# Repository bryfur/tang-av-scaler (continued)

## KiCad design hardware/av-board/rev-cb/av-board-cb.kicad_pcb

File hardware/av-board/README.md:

# The AV board (rev C-B)

The scaler's hardware, for the sixth generation of game consoles: a Sipeed Tang Mega 138K SOM (Gowin
GW5AST-138, with its DDR3 and configuration flash) on a carrier of its own, 100 x 100 mm, four
layers, about 290 parts. Built (JLCPCB) and running the scaler since 2026-11.

| On the board | Part | For |
|---|---|---|
| Component video in (three RCA jacks) | ADV7181D decoder | the console's YPbPr, sampled line-locked: 16-bit 4:2:2 to the FPGA; also wired: RGB with SCART sync, a VGA header (RGBHV with DDC): not used by the gateware yet |
| Stereo audio in (two RCA jacks) | PCM1808 converter, on its own 4.5 V supply | the console's sound, to HDMI |
| S/PDIF in (a header: coax or an optical module) | a slicer | not used by the gateware yet |
| HDMI out | SN65DP159 between the FPGA's transceivers and the receptacle (run as a redriver), ESD arrays, DDC/HPD/CEC | up to 4K60 by the link's rate; the scaler sends 1080p60 |
| Clock | MS5351M generator | the transceivers' reference, trimmed by the scaler to keep the output in step with the input; the audio converter's clock |
| Control | a Seeed XIAO ESP32-C5 in sockets, through level translators | Wi-Fi and the web page; the FPGA's JTAG (it loads bitstreams) and a UART and SPI port to it |
| Power | USB-C, 5 V / 3 A; a buck and LDOs | 3.3 V, 1.8 V, 1.1 V and the analogue rails |
| Test access | J17 (I2C buses and six spare FPGA pins behind 220 R), J16 (JTAG), rail test pads | [rev-cb/README.md](rev-cb/README.md) |

The design, connection by connection with its sources: [rev-c/design.md](rev-c/design.md) (the
SOM's interface, power, the clock generator, the XIAO, HDMI) and, for the circuits taken from the
earlier rev B (the decoder's front end, the audio converter, the supplies),
[older/rev-b/design.md](older/rev-b/design.md). Reviewed against every part's data sheet:
[rev-c/review.md](rev-c/review.md), [older/rev-b/review.md](older/rev-b/review.md). Fab files and
ordering notes: [rev-cb/README.md](rev-cb/README.md). The FPGA's pins:
`rev-cb/fpga/av-board-cb.cst` (generated from the board).

The board is generated with KiCad's Python API from `rev-cb/board.py`; nothing is drawn by hand.

## Layout of this directory

| Path | What |
|---|---|
| `rev-cb/` | the board: `board.py` (its parts and nets: the one source the schematic and PCB are generated from), `gen_pcb.py` (outline, placement, routing passes), the generated KiCad project, `fab/` (JLCPCB Gerbers, BOM, CPL), `img/` (renders), `fpga/` (pin constraints) |
| `rev-c/` | what rev C-B shares with its sibling C-A: the circuit (`carrier.py`), floor plan and layout, the SOM's interface (`som.py`, `som-pinout.csv`, `check_som_fp.py`), the FPGA pin assignment (`pinmap.py`), `design.md`, `review.md` |
| `kit/` | the generators and checks (below), and the circuits and layout taken from rev B: `circuits.py` (the supplies, the ADV7181D front end, the PCM1808, the S/PDIF input, the XIAO, the HDMI receptacle), `adv7181d_layout.py`, `tmds_layout.py` |
| `lib/` | LCSC symbols and footprints (3D models not in git) |
| `refs/` | data sheets and reference designs (not in git) |
| `older/` | the revisions before this one (A, B: hats on Sipeed's Tang Console; C-A: with an ADV7511): not built, kept for their design notes and reviews. [older/README.md](older/README.md) |

## Making the board

Everything is generated from `rev-cb/board.py`; edit that (and `gen_pcb.py` for placement), not
the KiCad files. On a machine with KiCad 9 (here: the build host), from this directory:

| Step | Command | Makes |
|---|---|---|
| check the design | `python3 rev-cb/board.py` | errors: one-pin nets, chip pins left open that should not be |
| schematic | `python3 kit/gen_sch.py rev-cb` | `rev-cb/av-board-cb.kicad_sch`, project and library tables |
| ERC | `kicad-cli sch erc rev-cb/av-board-cb.kicad_sch` | (clean) |
| netlist check | `kicad-cli sch export netlist -o /tmp/av.net rev-cb/av-board-cb.kicad_sch && python3 kit/check_netlist.py rev-cb /tmp/av.net` | schematic = board.py, pin by pin |
| PCB | `python3 rev-cb/gen_pcb.py --route` | `rev-cb/av-board-cb.kicad_pcb`: placed, fanned out, routed, ground poured, the revision's own pass, then whatever is left unconnected finished by mazeroute.py (`--complete`). Router: Freerouting (`FREEROUTING=1.9.0` default, under a private Xvfb; `2.5.0` headless), or DeepPCB (`ROUTER=deeppcb MINUTES=60`, API key in `~/.config/deeppcb/key`), or any session (`SES=file.ses`); a session from elsewhere gets a Freerouting finishing pass with its copper fixed (`FINISH=0`: none); `PCB=path` for a trial board elsewhere; `--silk`: the silkscreen pass again on a routed board; `--move REF x y angle`, then `--complete`: one part moved on a routed board, its connections made again |
| finishing | `kicad-cli pcb drc ...`, then for each connection left: `python3 kit/mazeroute.py dump BOARD REF.PAD REF.PAD /tmp/m.json [PARTNER_NET] && ~/tools/eda-venv/bin/python kit/mazeroute.py route /tmp/m.json /tmp/p.json && python3 kit/mazeroute.py apply BOARD /tmp/p.json` | a grid router (A*) for what Freerouting leaves: F/In2/B (`MAZE_LAYERS`, `MAZE_WIDTH`), new vias where they fit, our clearances; with `MAZE_SOFT=1` it may cross other signal nets' unlocked copper at a cost, and apply takes up what it crossed (rip-up). `gen_pcb.py --complete` does all this for whatever DRC lists, the rip-up last; DRC after |
| a router's result for some nets | `python3 kit/sesgraft.py BOARD x.ses PREFIX` | those nets' copper from a session added to a routed board |
| keep-outs on a routed board | `python3 rev-cb/gen_pcb.py --keepouts && python3 rev-cb/gen_pcb.py --complete` | after a change to the keep-outs (kit/tmds_layout.py's along the TMDS pairs: other lines 30 mil off, the arrays' pads voided in the planes): the board's own taken off, made again from its locked lines, the copper they now hold out taken up; `--complete` routes those connections again. The rest of the route stays |
| placement check | `python3 kit/placecheck.py rev-cb [--min 8]` | the small parts' signal pins far from the rest of their net (a part by the wrong anchor); `gen_pcb.py` itself prints the crossings left in each header bus |
| analog isolation | `python3 kit/xtalk.py rev-cb` | each analog line's digital neighbours within 1 mm on its layer: the closest gap, how far they run within 1 mm and within 0.5 mm |
| HDMI layout | `python3 kit/hdmi_audit.py rev-cb` | the TMDS pairs (and on rev C-B the transceivers' lanes and reference clock) against TI's layout rules (SN65DP159 12.1, SPRAAR7) and the HDMI skew budgets: lengths, skew, vias, turns, other copper along the run, crystals, switchers and holes nearby, the ground plane's edges and voids under the lines, the planes voided under parts on them; each finding with its rule |
| renders | `python3 kit/render.py rev-cb` | `rev-cb/img/`: a 3D view and a top view (KiCad's raytracer; models from `fetch_lib.sh` and `kit/fetch_3d.py`) |
| picture | `python3 kit/snap.py BOARD out.png` | a PNG of the board (needs PyMuPDF in `~/tools/eda-venv`) |
| DRC | `kicad-cli pcb drc BOARD` | |
| fab files | `python3 kit/gen_fab.py rev-cb` | `rev-cb/fab/`: Gerbers + drill zip, JLCPCB BOM and CPL, all from the board's lower-left corner; a BOM + CPL per assembly variant (`VARIANTS` in board.py: parts left for hand soldering) |
| parts library | `./kit/fetch_lib.sh` | `lib/`: LCSC symbols/footprints (committed) and 3D models (not) |

`kit/parts.py` is what board.py is written with (parts, LCSC numbers);
`kit/pcbkit.py` the PCB generator (placer, fanout, rules, planes, routing passes, silkscreen);
`kit/doubled.py` connections a router laid twice (loops, lengths counted twice, copper slivers);
`kit/decouple.py` each chip's supply pins and their capacitors (distances; regulators' in and out);
`kit/sexp.py` reads and writes KiCad's s-expression files; `kit/fix_lib.py` makes the LCSC
symbols' pins passive (their EasyEDA pin types are arbitrary); `kit/merge_sym.py` adds a symbol
whose EasyEDA name clashes with one already there; `kit/deeppcb.py` drives DeepPCB.

## Reference documents

In `refs/` (not in git). Every circuit on the board follows these (the ADV7842's and the ADV7511's are the older revisions').

| File | What | From |
|---|---|---|
| ADV7842_datasheet_adi.pdf | ADV7842 data sheet, Rev B: supplies, currents, crystal (28.63636 MHz), 256-ball map | analog.com data-sheets/ADV7842.pdf |
| UG-214_ADV7842_hardware.pdf | ADV7842 Hardware User Guide: analog input configuration (6.2.1), reset, pixel port, PCB layout recommendations, recommended decoupling (Fig. 168, 179), 75 R input termination (Appendix B) | analog.com user-guides/UG-214.pdf (via docs.ampnuts.ru mirror) |
| HDMI_RX_PowerSupplies_RevA_050411.pdf | ADI "PCB Layout and Power Supply Design Recommendations for HDMI RX Products", Rev A (April 2011): a ferrite per supply rail (Murata NFE61PT472C1H9), 10 nF + 100 nF per pin, 10 uF bulk on AVDD/CVDD/PVDD, LDOs not switchers, 3.3 V before 1.8 V; Fig. 2 the reference LDO supply (10 uH + 10 uF after the 1.8 V LDO, 100 nF + 1 uF on AVDD/CVDD/PVDD, 100 nF on DVDD/DVDDIO/TVDD, 1.8 V enable from 3.3 V via 100 k / 470 nF) | ADI EngineerZone, ADV7842 design support files (downloaded by hand) |
| adv7844ebz/ | ADI's ADV7844 evaluation board ("ADV7844 Input Module", Rev C, July 2010): schematic (11 sheets, image-only PDF), manufacturing BOM (.xls), IPC-356 netlist, Gerbers. The main circuit reference: see reference-notes.md | ADI EngineerZone, ADV7844 evaluation board info (downloaded by hand) |
| ADV7844-VER.5.8c.txt | ADI's recommended register scripts for the ADV7844 (v5.8c, 2012), the ADV7842's sibling: I2C write sequences per input mode, configuring the receiver (0x40 IO, 0x44 CP, 0x4C AFE ...) and the ADV7511 (0x72) together; "CP YPbPr SD/ED/HD" are the PS2's component modes. For bring-up; the ADV7842's own file (Rev 1.9) is the exact match | ADI EngineerZone, ADV7842 design support files (downloaded by hand) |
| UG-206_ADV7842_software.pdf | ADV7842 software (register) guide | analog.com user-guides/UG-206.pdf |
| UG-235_eval_ADV7842_7511.pdf | EVAL-ADV7842-7511 user guide (placement drawing, jumpers; no schematic) | farnell.com mirror of UG-235 |
| ADV7511_hardware_users_guide_RevD.pdf | ADV7511 Hardware User's Guide, Rev D: 100-lead LQFP pinout, input/output connections, HPD, DDC, PLL circuit, power domains and filtering, example schematic (Fig. 27) | analog.com user-guides/ADV7511_Hardware_Users_Guide.pdf |
| ADV7511_programming_guide.pdf | ADV7511 Programming Guide | analog.com user-guides |
| ADV7511_HDMI_designs_appnote.pdf | HDMI-enabled designs using the ADV7511 | analog.com evaluation-documentation |
| ADV7511W_hardware_users_guide_RevA.pdf | ADV7511W (64-lead) guide: cross-check only, its pinout does not apply | digikey.com |
| ADV7511_datasheet.pdf | ADV7511 short data sheet | docs.ampnuts.ru mirror |
| ADV7181D_datasheet.pdf | ADV7181D data sheet, Rev C (2024): 64-lead LFCSP pinout, supplies, component formats (525i-1080i), typical connection diagram (Fig. 9: ADC reference caps, loop filter, crystal), pixel output modes (rev B) | analog.com data-sheets/ADV7181D.pdf (downloaded by hand) |
| AN-1260.pdf | Crystal design considerations for ADI video decoders and HDMI parts | docs.ampnuts.ru mirror |
| AN-1270.pdf | ADV7511-based video generators | docs.ampnuts.ru mirror |
| AN-1143.pdf | ADV7511 HDCP 1.1 enable/disable | docs.ampnuts.ru mirror |
| PCM1808_datasheet.pdf | TI PCM1808 (Rev B): typical application circuit | ti.com |
| console138k_C.pdf | Sipeed Tang_138K_Console_V32001C schematic | dl.sipeed.com TANG/Console/02_Schematic |
| ibom_C.html | Sipeed's interactive BOM for board 32001C (part positions) | dl.sipeed.com TANG/Console/03_Designator_drawing |
| console/ | the Tang Mega 138K SOM's drawing, the NEO Console's schematic, the Retro Console's STEP model | dl.sipeed.com |
| RCJ-01.pdf | CUI RCJ-01x RCA jacks: footprint, colour codes | cuidevices.com |
| tlv62569.pdf, tps7a7001.pdf, tps7a20.pdf, tpd1e05u06.pdf, tpd4e05u06.pdf | TI: the buck, the LDOs, the ESD diodes and arrays | ti.com |
| sn65dp159.pdf | TI SN65DP159 retimer, SLLSEJ2G (rev C-B) | ti.com |
| MS5351M_datasheet_V1.4.pdf | Relmon MS5351M clock generator, V1.4 (Chinese): supplies, crystal, outputs (rev C) | LCSC (atta.szlcsc.com) |
| gowin/DS1239E.pdf | Gowin GW5AST data sheet DS1239: I/O standards, transceiver DC and reference clock characteristics (rev C) | cdn.gowinsemi.com.cn |

Still wanted, for cross-checking: the ADV7842 recommended settings (Rev 1.9) and the ADV7511
evaluation schematic (ADI's design support files).

What these documents say, circuit by circuit: [rev-c/design.md](rev-c/design.md) and [older/rev-b/design.md](older/rev-b/design.md) (rev C-B's circuits), [older/rev-a/reference-notes.md](older/rev-a/reference-notes.md) (ADV7842, ADV7511).

Fetching: analog.com serves its PDFs to `wget` (HTTP/1.1); curl over HTTP/2 stalls. EngineerZone
(ez.analog.com) refuses automated clients ("Access Denied"): its files are downloaded by hand.
Sipeed's file server lists folders with a POST to `https://dl.sipeed.com/fileList/<path>`.

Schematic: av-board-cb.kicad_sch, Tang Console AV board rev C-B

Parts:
C1, C2: 47u; C_1206_3216Metric; LCSC C96123
C3, C17, C18, C19, C24, C25, C27, C30, C33, C35, C38, C39, C40, C41, C42, C44, C46, C48, C50, C52, C55, C57, C59, C65, C66, C67, C68, C69, C71, C72, C73, C74, C75, C80, C81, C82, C83, C87, C88, C89, C90, C91, C92, C93, C94, C95, C97, C98, C101, C102, C103, C104, C105: 100n; C_0402_1005Metric; LCSC C1525
C4, C6, C7, C9, C10, C12, C70, C84, C85: 10u; C_0805_2012Metric; LCSC C15850
C5, C86: 6.8p; C_0402_1005Metric; LCSC C1576
C8, C11, C61, C63: 220p; C_0402_1005Metric; LCSC C1530
C13, C14, C15, C16, C56, C58, C60, C77, C79, C96, C100: 10u; C_0603_1608Metric; LCSC C19702
C20, C21: 1n; C_0402_1005Metric; LCSC C1523
C22, C23: 33p; C_0402_1005Metric; LCSC C1562
C26, C29, C32, C34: 10u; C_0402_1005Metric; LCSC C15525
C28, C31, C37, C43, C45, C47, C49, C51, C53, C99, C106, C107: 10n; C_0402_1005Metric; LCSC C15195
C36: 82n; C_0402_1005Metric; LCSC C277511
C54, C62, C64, C76, C78: 1u; C_0603_1608Metric; LCSC C15849
C108, C109, C110, C111: 22u; C_0805_2012Metric; LCSC C45783
D1, D3: B5819W; D_SOD-123; LCSC C8598
D2, D4, D5: KT-0603R; LED-SMD_L1.6-W0.8-R-RD; LCSC C2286
D6: SMF5.0A; D_SMF; LCSC C2857263
D7: 1N4148WS; D_SOD-323; LCSC C2128
D8, D9, D10, D11, D12, D13: TPD1E05U06DPYR; X1SON-2_L1.0-W0.6-P0.65-RD-1; LCSC C436349
F1: 3A; Fuse_1812_4532Metric; LCSC C18198349
F2, F3: 0.2A; F0805; LCSC C883105
FB1, FB2, FB3, FB4: 120R; L_0603_1608Metric; LCSC C14709
J1: RCA Y; CONN-TH_RCJ-011; LCSC C4991844
J2: RCA Pb; CONN-TH_RCJ-011; LCSC C4991844
J3: RCA Pr; CONN-TH_RCJ-011; LCSC C4991691
J4: RCA L; CONN-TH_RCJ-011; LCSC C4991844
J5: RCA R; CONN-TH_RCJ-011; LCSC C4991691
J6: HDMI-001; HDMI-SMD_19P-P0.50-H-F; LCSC C138388
J7: SYNC; HDR-TH_2P-P2.54-V-M; LCSC C492401
J8: VGA; HDR-TH_16P-P2.54-V-M-R2-C8-S2.54; LCSC C68234
J11: XIAO 5V..D7; HDR-TH_7P-P2.54-V-F; LCSC C22438157
J12: XIAO D0..D6; HDR-TH_7P-P2.54-V-F; LCSC C22438157
J13: SPDIF; HDR-TH_5P-P2.54-V-M; LCSC C492404
J15: USB-C 5V; USB-C_SMD-TYPE-C-31-M-12_1; LCSC C165948
J16: JTAG; HDR-TH_6P-P2.54-V-M; LCSC C492405
J17: DEBUG; HDR-TH_16P-P2.54-V-M-R2-C8-S2.54; LCSC C68234
J20: DF40HC(3.0)-80DS; DF40HC-3.0-80DS-SOM; LCSC C2858577
J21, J22: DF40HC(3.0)-100DS; DF40HC-3.0-100DS-SOM; LCSC C424649
L1, L2: 2.2uH; IND-SMD_L3.0-W3.0_FNR30XXS; LCSC C167747
Q1, Q2, Q3, Q4, Q5: 2N7002; SOT-23-3_L2.9-W1.3-P1.90-LS2.4-BR; LCSC C8545
R1, R2, R114, R115: 5.1k; R_0402_1005Metric; LCSC C25905
R3: 499k; R_0402_1005Metric; LCSC C25793
R4, R51, R53, R91: 100k; R_0402_1005Metric; LCSC C25741
R5: 169k; R_0402_1005Metric; LCSC C25758
R6, R8: 30.1k; R_0402_1005Metric; LCSC C29402
R7: 78.7k; R_0402_1005Metric; LCSC C67239
R9, R10, R11, R12, R30, R31, R32, R48: 75; R_0603_1608Metric; LCSC C4275
R13, R49: 1M; R_0402_1005Metric; LCSC C26083
R14: 1.69k; R_0402_1005Metric; LCSC C25870
R15, R16, R17, R18, R19, R20, R21, R22, R35, R36, R50, R52, R87: 33; R_0402_1005Metric; LCSC C25105
R23, R24, R25, R26, R27, R28, R37, R39, R85, R86, R96, R97: 4.7k; R_0402_1005Metric; LCSC C25900
R29, R33, R34, R41, R42, R43, R45, R47, R58, R59, R60, R61, R62, R63, R64, R65, R66, R67, R68, R69, R70, R71, R72, R73, R74, R76, R78, R79, R83, R94, R95, R99: 10k; R_0402_1005Metric; LCSC C25744
R38, R40: 47k; R_0402_1005Metric; LCSC C25792
R44, R46: 12k; R_0402_1005Metric; LCSC C25752
R54, R55, R56, R57, R75, R77, R80: 470; R_0402_1005Metric; LCSC C25117
R81, R82, R92, R93: 2k; R_0402_1005Metric; LCSC C4109
R84: 27k; R_0402_1005Metric; LCSC C25771
R88, R89: 2.2; R_0402_1005Metric; LCSC C2909330
R90: 82.5k; R_0402_1005Metric; LCSC C11717
R98: 7.06k; R_0402_1005Metric; LCSC C853722
R100, R101, R102, R103, R104, R105, R106, R107, R108, R109, R110, R111, R112: 220; R_0402_1005Metric; LCSC C25091
R113: 1k; R_0402_1005Metric; LCSC C11702
RN1, RN2, RN3: 33; RES-ARRAY-SMD_0402-8P-L2.0-W1.0-BL; LCSC C25501
SO1, SO2, SO3, SO4: M2 spacer 3mm; SOM-M2-Hole
SW1, SW2, SW3: TS-1187A-B-A-B; SW-SMD_4P-L5.1-W5.1-P3.70-LS6.5-TL_H1.5; LCSC C318884
TP1: +5V; TestPoint_Pad_D1.5mm
TP2: 3V6; TestPoint_Pad_D1.5mm
TP3: 3V3; TestPoint_Pad_D1.5mm
TP4: 1V8A; TestPoint_Pad_D1.5mm
TP5: 1V1; TestPoint_Pad_D1.5mm
TP6: 3V0; TestPoint_Pad_D1.5mm
TP7: 2V5; TestPoint_Pad_D1.5mm
TP8: 5VA; TestPoint_Pad_D1.5mm
TP9, TP10: GND; TestPoint_THTPad_D2.0mm_Drill1.0mm
U1: ADV7181DBCPZ-RL; LFCSP-64_L9.0-W9.0-P0.50-BL-EP7.1; LCSC C514378
U2: SN65DP159RGZR; VQFN-48_L7.0-W7.0-P0.50-BL-EP4.1; LCSC C179676
U3: PCM1808PWR; TSSOP-14_L5.0-W4.4-P0.65-LS6.4-BL; LCSC C55513
U4, U7: TLV62569DBVR; SOT-23-5_L3.0-W1.7-P0.95-LS2.8-BR; LCSC C141836
U5, U6: TPS7A7001DDAR; SOIC-8_L4.9-W3.9-P1.27-LS6.0-BL-EP; LCSC C60719
U8, U9, U10, U19, U20: TPD4E05U06DQAR; USON-10_L2.5-W1.0-P0.50-BL; LCSC C138714
U12: TPS7A2045PDBVR; SOT-23-5_L2.9-W1.6-P0.95-LS2.8-BR; LCSC C2873627
U13: SN74LVC1GU04DBVR; SOT-23-5_L3.0-W1.7-P0.95-LS2.8-BR; LCSC C81934
U14, U15: SN74LVC1G04DBVR; SOT-23-5_L3.0-W1.7-P0.95-LS2.8-BR; LCSC C7827
U17: MS5351M; MSOP-10_L3.0-W3.0-P0.50-LS5.0-BL; LCSC C1509083
U18: ME6211C25M5G-N; SOT-23-5_L3.0-W1.7-P0.95-LS2.8-BR; LCSC C194395
U21: SN74LVC2G17DBVR; SOT-23-6_L2.9-W1.6-P0.95-LS2.8-BL; LCSC C10429
U22: SN74LVC8T245PWR; TSSOP-24_L7.8-W4.4-P0.65-LS6.4-BL; LCSC C27643
U23: SN74AVC4T245PWR; TSSOP-16_L5.0-W4.4-P0.65-LS6.4-BL; LCSC C81461
U24: ME6211C30M5G-N; SOT-23-5_L2.9-W1.6-P0.95-LS2.8-BL; LCSC C403651
Y1: 28.63636MHz 20pF; CRYSTAL-SMD_L5.0-W3.2; LCSC C112564
Y2: 25MHz 10pF; CRYSTAL-SMD_4P-L2.0-W1.6-BL; LCSC C5265839

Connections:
1V1: C85.1, C86.1, C100.1, C101.1, C102.1, C103.1, C104.1, C105.1, C106.1, C107.1, L2.2, R90.1, TP5.1, U2.14 (VDD), U2.23 (VDD), U2.24 (VDD), U2.37 (VDD), U2.48 (VDD)
1V8A: C11.1, C12.1, D1.2 (A), FB1.1, FB2.1, R7.1, TP4.1, U6.6 (OUT)
2V5: C79.1, C81.1, TP7.1, U17.7 (VDDO), U18.5 (VOUT)
3V0: C77.1, C80.1, TP6.1, U17.1 (VDD), U24.5 (VOUT)
3V3: C8.1, C9.1, C10.1, C41.1, C59.1, C60.1, C67.1, C68.1, C69.1, C72.1, C74.1, C76.1, C78.1, C96.1, C97.1, C98.1, C99.1, D1.1 (K), FB3.1, FB4.1, J16.1, Q1.1 (G), Q2.1 (G), Q5.1 (G), R5.1, R23.1, R24.1, R37.1, R39.1, R65.2, R67.2, R68.2, R69.2, R70.2, R71.2, R72.2, R73.1, R74.1, R75.1, R76.1, R77.1, R78.1, R79.1, R84.1, R85.1, R86.1, R92.1, R93.1, R94.1, R96.1, R97.1, R99.1, R100.1, R113.1, TP3.1, U2.13 (VCC), U2.43 (VCC), U3.4 (VDD), U5.6 (OUT), U6.2 (EN), U6.3 (IN), U13.5 (VCC), U14.5 (VCC), U15.5 (VCC), U18.1 (VIN), U18.3 (CE), U21.5 (VCC), U22.23 (VCCB), U22.24 (VCCB), U23.16 (VCCB), U24.1 (VIN), U24.3 (CE)
3V6: C5.1, C6.1, C7.1, L1.2, R3.1, TP2.1, U5.2 (EN), U5.3 (IN)
5VA: C57.1, C58.1, TP8.1, U3.3 (VCC), U12.5 (OUT)
+5V: C1.1, C2.1, C3.1, C4.1, C54.1, C84.1, C108.1, C109.1, C110.1, C111.1, D3.2 (A), F1.2, F2.1, F3.1, J22.89, J22.91, J22.93, J22.95, J22.97, J22.99, TP1.1, U4.1 (EN), U4.4 (VIN), U7.1 (EN), U7.4 (VIN), U12.1 (IN), U12.3 (EN)
AIN_PB: C18.2, U1.47 (AIN8)
AIN_PR: C19.2, U1.45 (AIN6)
AIN_VB: C40.2, U1.48 (AIN9)
AIN_VG: C39.2, U1.35 (AIN2)
AIN_VR: C38.2, U1.46 (AIN7)
AIN_Y: C17.2, U1.49 (AIN10)
ALSB: R27.2, U1.52 (ALSB)
AUD_DIV_L: C61.1, C62.1, R44.2, R45.1
AUD_DIV_R: C63.1, C64.1, R46.2, R47.1
AUD_VINL: C62.2, U3.13 (VINL)
AUD_VINR: C64.2, U3.14 (VINR)
AV_AVDD: C15.1, C52.1, C53.1, FB3.2, U1.41 (AVDD)
AV_C0: R19.1, U1.26 (P2)
AV_C1: R18.1, U1.25 (P3)
AV_C2: RN3.3, U1.19 (P4)
AV_C3: RN3.2, U1.18 (P5)
AV_C4: RN3.1, U1.17 (P6)
AV_C5: R17.1, U1.16 (P7)
AV_C6: R16.1, U1.15 (P8)
AV_C7: R15.1, U1.14 (P9)
AV_DE: R22.1, U1.63 (FIELD/DE)
AV_DVDD: C13.1, C46.1, C47.1, C48.1, C49.1, FB1.2, U1.23 (DVDD), U1.58 (DVDD)
AV_DVDDIO: C16.1, C42.1, C43.1, C44.1, C45.1, FB4.2, R26.1, R27.1, R28.1, U1.4 (DVDDIO), U1.11 (DVDDIO)
AV_HS: R20.1, U1.2 (HS/CS)
AV_LLC: RN3.4, U1.20 (LLC)
AV_PVDD: C14.1, C36.2, C37.2, C50.1, C51.1, FB2.2, U1.31 (PVDD)
AV_VS: R21.1, U1.64 (VS)
AV_Y0: RN2.4, U1.8 (P12)
AV_Y1: RN2.3, U1.7 (P13)
AV_Y2: RN2.2, U1.6 (P14)
AV_Y3: RN2.1, U1.5 (P15)
AV_Y4: RN1.4, U1.62 (P16)
AV_Y5: RN1.3, U1.61 (P17)
AV_Y6: RN1.2, U1.60 (P18)
AV_Y7: RN1.1, U1.59 (P19)
CAPC2: C29.1, C30.1, C31.1, U1.44 (CAPC2)
CAPY1: C26.1, C27.1, C28.1, U1.39 (CAPY1)
CAPY2: C24.1, C25.1, C26.2, C27.2, C28.2, C29.2, C30.2, C31.2, U1.40 (CAPY2)
CC1: J15.A5 (CC1), R1.1
CC2: J15.B5 (CC2), R2.1
CEC_FPGA: J21.53, Q5.2 (S), R99.2
CEC_PU: D7.2 (A), R84.2
CML: C34.1, C35.1, U1.43 (CML)
D4_A: D4.1 (A), R75.2
D4_K: D4.2 (K), Q3.3 (D)
D5_A: D5.1 (A), R77.2
D5_K: D5.2 (K), Q4.3 (D)
DBG0: J22.36, R107.1
DBG0_J: J17.9, R107.2
DBG1: J22.34, R108.1
DBG1_J: J17.10, R108.2
DBG2: J22.32, R109.1
DBG2_J: J17.11, R109.2
DBG3: J22.30, R110.1
DBG3_J: J17.12, R110.2
DBG4: J22.28, R111.1
DBG4_J: J17.13, R111.2
DBG5: J22.26, R112.1
DBG5_J: J17.14, R112.2
DBG_VREF: J17.1, R100.2
DDC_SCL: J21.60, R93.2, U2.46 (SCL_SRC)
DDC_SDA: J21.58, R92.2, U2.47 (SDA_SRC)
DP_A0: R95.1, U2.21 (EQ_SEL/A0)
DP_CK_N: C94.2, U2.12 (IN_CLKn)
DP_CK_P: C93.2, U2.11 (IN_CLKp)
DP_D0_N: C92.2, U2.9 (IN_D0n)
DP_D0_P: C91.2, U2.8 (IN_D0p)
DP_D1_N: C90.2, U2.6 (IN_D1n)
DP_D1_P: C89.2, U2.5 (IN_D1p)
DP_D2_N: C88.2, U2.3 (IN_D2n)
DP_D2_P: C87.2, U2.2 (IN_D2p)
DP_HPD: J21.49, U2.4 (HPD_SRC)
DP_I2C_EN: R94.2, U2.10 (I2C_EN/PIN)
DP_OE: C95.1, J21.62, U2.42 (OE)
DP_SCL: J21.47, R96.2, R103.1, U2.15 (SCL_CTL)
DP_SCL_J: J17.5, R103.2
DP_SDA: J21.43, R97.2, R104.1, U2.16 (SDA_CTL)
DP_SDA_J: J17.6, R104.2
DP_VSADJ: R98.1, U2.22 (VSADJ)
ELPF: C37.1, R14.1, U1.30 (ELPF)
ELPF_RC: C36.1, R14.2
ESP_CS: J22.2, R68.1, U22.18 (B4)
ESP_IRQ: J22.4, R70.1, U23.12 (1B2)
ESP_MISO: J22.14, R72.1, U23.10 (2B2)
ESP_MOSI: J22.16, U22.15 (B7)
ESP_RX: J22.10, R71.1, U23.11 (2B1)
ESP_SCK: J22.12, U22.16 (B6)
ESP_TX: J22.6, U22.17 (B5)
FB_1V1: C86.2, R90.2, R91.1, U7.5 (FB)
FB_1V8A: C11.2, R7.2, R8.1, U6.7 (FB)
FB_3V3: C8.2, R5.2, R6.1, U5.7 (FB)
FB_3V6: C5.2, R3.2, R4.1, U4.5 (FB)
FMT: R43.1, U3.12 (FMT)
FPGA_DONE: J20.77, Q3.1 (G), R74.2
FPGA_READY: J20.79, Q4.1 (G), R76.2
GND: C1.2, C2.2, C3.2, C4.2, C6.2, C7.2, C9.2, C10.2, C12.2, C13.2, C14.2, C15.2, C16.2, C22.2, C23.2, C24.2, C25.2, C32.2, C33.2, C34.2, C35.2, C41.2, C42.2, C43.2, C44.2, C45.2, C46.2, C47.2, C48.2, C49.2, C50.2, C51.2, C52.2, C53.2, C54.2, C55.2, C56.2, C57.2, C58.2, C59.2, C60.2, C61.2, C63.2, C65.2, C67.2, C68.2, C69.2, C70.2, C71.2, C72.2, C73.2, C74.2, C75.2, C76.2, C77.2, C78.2, C79.2, C80.2, C81.2, C84.2, C85.2, C95.2, C96.2, C97.2, C98.2, C99.2, C100.2, C101.2, C102.2, C103.2, C104.2, C105.2, C106.2, C107.2, C108.2, C109.2, C110.2, C111.2, D2.2 (K), D6.2 (A), D8.2 (GND), D9.2 (GND), D10.2 (GND), D11.2 (GND), D12.2 (GND), D13.2 (GND), J1.1, J2.1, J3.1, J4.1, J5.1, J6.2 (TMDSData2Shield), J6.5 (TMDSData1Shield), J6.8 (TMDSData0Shield), J6.11 (TMDSClockShield), J6.17 (DDC/CECGround), J6.20, J6.21, J6.22, J6.23, J7.2, J8.5, J8.6, J8.7, J8.8, J8.10, J11.2, J13.2, J13.4, J15.1 (EH), J15.2 (EH), J15.3 (EH), J15.4 (EH), J15.A1B12 (GND), J15.B1A12 (GND), J16.2, J17.2, J17.15, J17.16, J20.1, J20.2, J20.8, J20.11, J20.16, J20.17, J20.21, J20.22, J20.27, J20.35, J20.38, J20.60, J20.63, J20.66, J21.2, J21.3, J21.8, J21.9, J21.14, J21.15, J21.20, J21.21, J21.26, J21.27, J21.32, J21.33, J21.38, J21.39, J21.45, J21.46, J21.51, J21.57, J21.63, J21.69, J21.70, J21.75, J21.76, J21.81, J21.82, J21.87, J21.88, J21.93, J21.94, J21.99, J21.100, J22.47, J22.53, J22.59, J22.65, J22.77, J22.79, J22.81, J22.83, J22.85, J22.87, J22.100, Q3.2 (S), Q4.2 (S), R1.2, R2.2, R4.2, R6.2, R8.2, R9.2, R10.2, R11.2, R12.2, R25.2, R29.2, R30.2, R31.2, R32.2, R33.2, R34.2, R41.2, R42.2, R43.2, R45.2, R47.2, R48.2, R51.2, R53.2, R59.2, R64.2, R66.2, R83.2, R91.2, R95.2, R98.2, R114.2, R115.2, SO1.1, SO2.1, SO3.1, SO4.1, SW1.4 (D), SW2.4 (D), SW3.4 (D), TP9.1, TP10.1, U1.3 (GND), U1.10 (GND), U1.24 (GND), U1.57 (GND), U1.65 (EP), U2.7 (GND), U2.19 (GND), U2.30 (GND), U2.41 (GND), U2.49 (EP), U3.2 (AGND), U3.5 (DGND), U4.2 (GND), U5.1 (NC), U5.4 (NC), U5.5 (NC), U5.8 (GND), U5.9 (EP), U6.1 (NC), U6.4 (NC), U6.5 (NC), U6.8 (GND), U6.9 (EP), U7.2 (GND), U8.3 (GND), U8.8 (GND), U9.3 (GND), U9.8 (GND), U10.3 (GND), U10.8 (GND), U12.2 (GND), U13.3 (GND), U14.3 (GND), U15.3 (GND), U17.8 (GND), U18.2 (VSS), U19.3 (GND), U19.8 (GND), U20.3 (GND), U20.8 (GND), U21.2 (GND), U22.10 (A8), U22.11 (GND), U22.12 (GND), U22.13 (GND), U22.22 (~OE), U23.2 (1DIR), U23.3 (2DIR), U23.8 (GND), U23.9 (GND), U23.14 (2#OE), U23.15 (1#OE), U24.2 (VSS), Y2.2 (GND), Y2.4 (GND)
HDMI_5V: C75.1, F3.2, J6.18 (+5VPower), R81.1, R82.1
HDMI_CEC: D7.1 (K), J6.13 (CEC), Q5.3 (D), U8.5 (D2-), U8.6 (NC)
HDMI_HPD: J6.19 (HotPlugDetect), R83.1, U2.33 (HPD_SNK), U8.4 (D2+), U8.7 (NC)
HDMI_SCL: J6.15 (SCL), R81.2, U2.38 (SCL_SNK), U8.1 (D1+), U8.10 (NC)
HDMI_SDA: J6.16 (SDA), R82.2, U2.39 (SDA_SNK), U8.2 (D1-), U8.9 (NC)
IN_BCK: J21.67, U3.8 (BCK)
IN_C0: J22.86, R19.2
IN_C1: J22.84, R18.2
IN_C2: J22.82, RN3.6
IN_C3: J22.63, RN3.7
IN_C4: J22.80, RN3.8
IN_C5: J22.78, R17.2
IN_C6: J22.61, R16.2
IN_C7: J22.76, R15.2
IN_DE: J22.56, R22.2
IN_DOUT: J21.65, U3.9 (DOUT)
IN_HS: J22.62, R20.2
IN_INT: J22.60, R26.2, U1.1 (#INT)
IN_KEY1: J20.75, R78.2, SW1.1 (A)
IN_KEY2: J20.73, R79.2, SW2.1 (A)
IN_LED: J20.71, R80.1
IN_LLC: J22.88, RN3.5
IN_LRCK: J21.66, U3.7 (LRCK)
IN_RESET_N: J22.90, R25.1, U1.51 (#RESET)
IN_SCKI: J21.68, U3.6 (SCKI)
IN_SCL: J22.44, R23.2, R101.1, U1.54 (SCLK)
IN_SCL_J: J17.3, R101.2
IN_SDA: J22.42, R24.2, R102.1, U1.53 (SDATA)
IN_SDA_J: J17.4, R102.2
IN_VS: J22.58, R21.2
IN_Y0: J22.74, RN2.5
IN_Y1: J22.68, RN2.6
IN_Y2: J22.66, RN2.7
IN_Y3: J22.64, RN2.8
IN_Y4: J22.54, RN1.5
IN_Y5: J22.52, RN1.6
IN_Y6: J22.48, RN1.7
IN_Y7: J22.46, RN1.8
JTAG_TCK: J16.3, J20.7, R66.1, U22.20 (B2)
JTAG_TDI: J16.5, J20.9, R67.1, U22.19 (B3)
JTAG_TDO: J16.4, J20.5, R69.1, U23.13 (1B1)
JTAG_TMS: J16.6, J20.3, R65.1, U22.21 (B1)
LED_A: D2.1 (A), R80.2
MD0: R41.1, U3.10 (MD0)
MD1: R42.1, U3.11 (MD1)
MODE0: J22.73, R113.2
MODE1: J22.71, R114.1
MODE2: J22.69, R115.1
PD_FB: R29.1, U1.32 (FB)
PLL_CLK0: R88.1, U17.10 (CLK0)
PLL_CLK0_S: C82.1, R88.2
PLL_CLK1: R89.1, U17.9 (CLK1)
PLL_CLK1_S: C83.1, R89.2
PLL_CLK2: J21.31, R87.2
PLL_CLK2_S: R87.1, U17.6 (CLK2)
PLL_SCL: J21.64, R85.2, R105.1, U17.4 (SCL)
PLL_SCL_J: J17.7, R105.2
PLL_SDA: J21.55, R86.2, R106.1, U17.5 (SDA)
PLL_SDA_J: J17.8, R106.2
PLL_XA: U17.2 (XA), Y2.1
PLL_XB: U17.3 (XB), Y2.3
PWRDWN: R28.2, U1.29 (#PWRDWN)
RCA_L: J4.2, R44.1
RCA_PB: C18.1, D9.1 (I/O), J2.2, R10.1
RCA_PR: C19.1, D10.1 (I/O), J3.2, R11.1
RCA_R: J5.2, R46.1
RCA_SYNC: C21.1, D11.1 (I/O), J7.1, R12.1
RCA_Y: C17.1, C20.1, D8.1 (I/O), J1.2, R9.1
RECONFIG_N: J20.61, R73.2, SW3.1 (A)
REFOUT: C32.1, C33.1, U1.42 (REFOUT)
SER_CK_N: C94.1, J21.77
SER_CK_P: C93.1, J21.79
SER_D0_N: C92.1, J21.83
SER_D0_P: C91.1, J21.85
SER_D1_N: C90.1, J21.89
SER_D1_P: C89.1, J21.91
SER_D2_N: C88.1, J21.95
SER_D2_P: C87.1, J21.97
SER_REFCLK_N: C83.2, J21.96
SER_REFCLK_P: C82.2, J21.98
SPDIF_5V: C65.1, F2.2, J13.5
SPDIF_AC: C66.2, R49.2, U13.2 (A)
SPDIF_AMP: R49.1, U13.4 (Y), U14.2 (A)
SPDIF_COAX: C66.1, D12.1 (I/O), J13.1, R48.1
SPDIF_OPT: D13.1 (I/O), J13.3, R51.1, U15.2 (A)
SPDIF_ORX: J21.59, R52.2
SPDIF_OSQ: R52.1, U15.4 (Y)
SPDIF_RX: J21.61, R50.2
SPDIF_SQ: R50.1, U14.4 (Y)
SW_1V1: L2.1, U7.3 (SW)
SW_3V6: L1.1, U4.3 (SW)
SYNC_G: C21.2, U1.33 (SOG)
SYNC_Y: C20.2, U1.50 (SOY)
TMDS_CK_N: J6.12 (TMDSClock-), U2.25 (OUT_CLKn), U10.5 (D2-), U10.6 (NC)
TMDS_CK_P: J6.10 (TMDSClock+), U2.26 (OUT_CLKp), U10.4 (D2+), U10.7 (NC)
TMDS_D0_N: J6.9 (TMDSData0-), U2.28 (OUT_D0n), U10.2 (D1-), U10.9 (NC)
TMDS_D0_P: J6.7 (TMDSData0+), U2.29 (OUT_D0p), U10.1 (D1+), U10.10 (NC)
TMDS_D1_N: J6.6 (TMDSData1-), U2.31 (OUT_D1n), U9.5 (D2-), U9.6 (NC)
TMDS_D1_P: J6.4 (TMDSData1+), U2.32 (OUT_D1p), U9.4 (D2+), U9.7 (NC)
TMDS_D2_N: J6.3 (TMDSData2-), U2.34 (OUT_D2n), U9.2 (D1-), U9.9 (NC)
TMDS_D2_P: J6.1 (TMDSData2+), U2.35 (OUT_D2p), U9.1 (D1+), U9.10 (NC)
VBUS_IN: D6.1 (K), F1.1, J15.A4B9 (VBUS), J15.B4A9 (VBUS)
VGA_5V: J8.9, R38.1, R40.1
VGA_B: C40.1, J8.3, R32.1, U19.5 (D2-), U19.6 (NC)
VGA_G: C39.1, J8.2, R31.1, U19.2 (D1-), U19.9 (NC)
VGA_HS: J8.13, R33.1, U20.1 (D1+), U20.10 (NC), U21.1 (1A)
VGA_HSB: R35.1, U21.6 (1Y)
VGA_HSIN: R35.2, U1.56 (HS_IN/CS_IN)
VGA_R: C38.1, J8.1, R30.1, U19.4 (D2+), U19.7 (NC)
VGA_SCL: J8.15, Q2.3 (D), R40.2, U20.5 (D2-), U20.6 (NC)
VGA_SCL_F: J22.38, Q2.2 (S), R39.2
VGA_SDA: J8.12, Q1.3 (D), R38.2, U20.4 (D2+), U20.7 (NC)
VGA_SDA_F: J22.40, Q1.2 (S), R37.2
VGA_VS: J8.14, R34.1, U20.2 (D1-), U20.9 (NC), U21.3 (2A)
VGA_VSB: R36.1, U21.4 (2Y)
VGA_VSIN: R36.2, U1.55 (VS_IN)
VREF: C55.1, C56.1, U3.1 (VREF)
XIAO_3V3: C71.1, C73.1, J11.3, R53.1, R58.2, R60.2, R61.2, R62.2, R63.2, U22.1 (VCCA), U22.2 (DIR), U23.1 (VCCA)
XIAO_5V: C70.1, D3.1 (K), J11.1
XIAO_D0: J12.1, R58.1, U22.3 (A1)
XIAO_D1: J12.2, R59.1, U22.4 (A2)
XIAO_D2: J12.3, R60.1, U22.5 (A3)
XIAO_D3: J12.4, R54.2
XIAO_D3_A: R54.1, U23.4 (1A1)
XIAO_D4: J12.5, R61.1, U22.6 (A4)
XIAO_D5: J12.6, R55.2
XIAO_D5_A: R55.1, U23.5 (1A2)
XIAO_D6: J12.7, R62.1, U22.7 (A5)
XIAO_D7: J11.7, R56.2
XIAO_D7_A: R56.1, U23.6 (2A1)
XIAO_D8: J11.6, R63.1, U22.8 (A6)
XIAO_D9: J11.5, R57.2
XIAO_D9_A: R57.1, U23.7 (2A2)
XIAO_D10: J11.4, R64.1, U22.9 (A7)
XTAL: C22.1, R13.1, U1.22 (XTAL), Y1.1 (OSC1)
XTAL1: C23.1, R13.2, U1.21 (XTAL1), Y1.2 (OSC2)

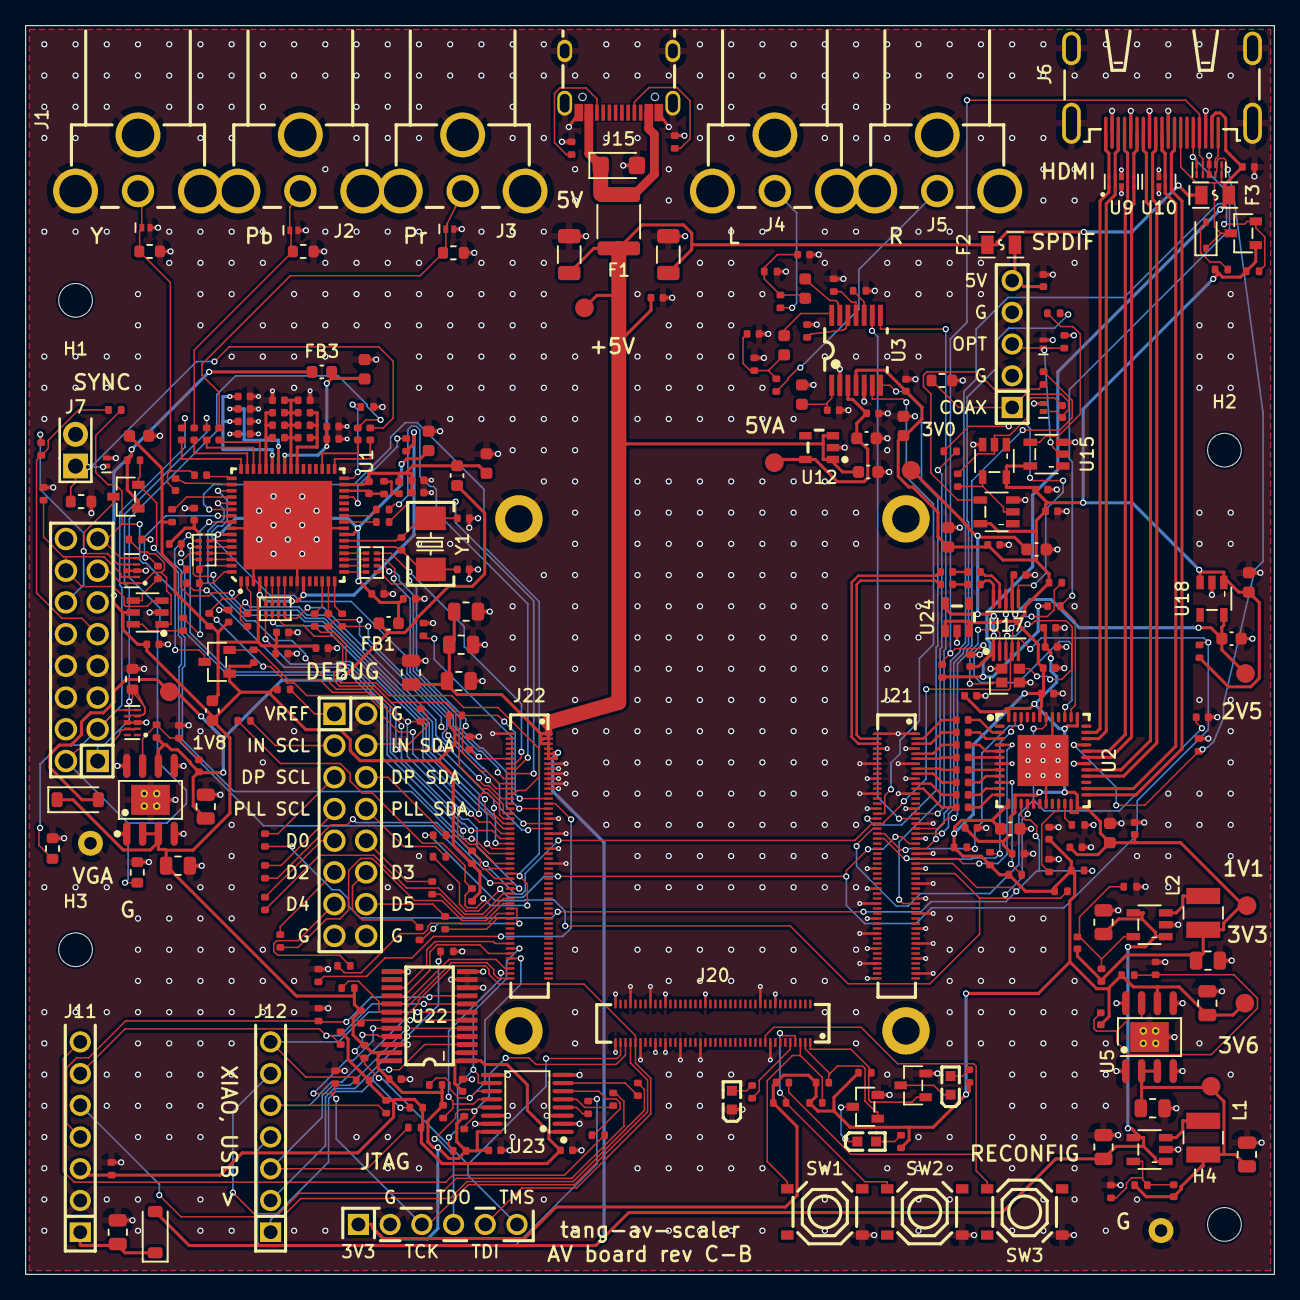
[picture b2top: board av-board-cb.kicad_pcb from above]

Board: 4 copper layers, 100.0 x 100.0 mm, 318 parts (0 on the bottom side), 240 nets.

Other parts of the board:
H1, H2, H3, H4: MountingHole_2.7mm_M2.5

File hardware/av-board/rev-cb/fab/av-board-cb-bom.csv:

Comment,Designator,Footprint,LCSC Part #
47u,"C1,C2",C_1206_3216Metric,C96123
100n,"C3,C17,C18,C19,C24,C25,C27,C30,C33,C35,C38,C39,C40,C41,C42,C44,C46,C48,C50,C52,C55,C57,C59,C65,C66,C67,C68,C69,C71,C72,C73,C74,C75,C80,C81,C82,C83,C87,C88,C89,C90,C91,C92,C93,C94,C95,C97,C98,C101,C102,C103,C104,C105",C_0402_1005Metric,C1525
10u,"C4,C6,C7,C9,C10,C12,C70,C84,C85",C_0805_2012Metric,C15850
6.8p,"C5,C86",C_0402_1005Metric,C1576
220p,"C8,C11,C61,C63",C_0402_1005Metric,C1530
10u,"C13,C14,C15,C16,C56,C58,C60,C77,C79,C96,C100",C_0603_1608Metric,C19702
1n,"C20,C21",C_0402_1005Metric,C1523
33p,"C22,C23",C_0402_1005Metric,C1562
10u,"C26,C29,C32,C34",C_0402_1005Metric,C15525
10n,"C28,C31,C37,C43,C45,C47,C49,C51,C53,C99,C106,C107",C_0402_1005Metric,C15195
82n,C36,C_0402_1005Metric,C277511
1u,"C54,C62,C64,C76,C78",C_0603_1608Metric,C15849
22u,"C108,C109,C110,C111",C_0805_2012Metric,C45783
B5819W,"D1,D3",D_SOD-123,C8598
KT-0603R,"D2,D4,D5",LED-SMD_L1.6-W0.8-R-RD,C2286
SMF5.0A,D6,D_SMF,C2857263
1N4148WS,D7,D_SOD-323,C2128
TPD1E05U06DPYR,"D8,D9,D10,D11,D12,D13",X1SON-2_L1.0-W0.6-P0.65-RD-1,C436349
3A,F1,Fuse_1812_4532Metric,C18198349
0.2A,"F2,F3",F0805,C883105
120R,"FB1,FB2,FB3,FB4",L_0603_1608Metric,C14709
RCA Y,J1,CONN-TH_RCJ-011,C4991844
RCA Pb,J2,CONN-TH_RCJ-011,C4991844
RCA Pr,J3,CONN-TH_RCJ-011,C4991691
RCA L,J4,CONN-TH_RCJ-011,C4991844
RCA R,J5,CONN-TH_RCJ-011,C4991691
HDMI-001,J6,HDMI-SMD_19P-P0.50-H-F,C138388
SYNC,J7,HDR-TH_2P-P2.54-V-M,C492401
VGA,J8,HDR-TH_16P-P2.54-V-M-R2-C8-S2.54,C68234
XIAO 5V..D7,J11,HDR-TH_7P-P2.54-V-F,C22438157
XIAO D0..D6,J12,HDR-TH_7P-P2.54-V-F,C22438157
SPDIF,J13,HDR-TH_5P-P2.54-V-M,C492404
USB-C 5V,J15,USB-C_SMD-TYPE-C-31-M-12_1,C165948
JTAG,J16,HDR-TH_6P-P2.54-V-M,C492405
DEBUG,J17,HDR-TH_16P-P2.54-V-M-R2-C8-S2.54,C68234
DF40HC(3.0)-80DS,J20,DF40HC-3.0-80DS-SOM,C2858577
DF40HC(3.0)-100DS,"J21,J22",DF40HC-3.0-100DS-SOM,C424649
2.2uH,"L1,L2",IND-SMD_L3.0-W3.0_FNR30XXS,C167747
2N7002,"Q1,Q2,Q3,Q4,Q5",SOT-23-3_L2.9-W1.3-P1.90-LS2.4-BR,C8545
5.1k,"R1,R2,R114,R115",R_0402_1005Metric,C25905
499k,R3,R_0402_1005Metric,C25793
100k,"R4,R51,R53,R91",R_0402_1005Metric,C25741
169k,R5,R_0402_1005Metric,C25758
30.1k,"R6,R8",R_0402_1005Metric,C29402
78.7k,R7,R_0402_1005Metric,C67239
75,"R9,R10,R11,R12,R30,R31,R32,R48",R_0603_1608Metric,C4275
1M,"R13,R49",R_0402_1005Metric,C26083
1.69k,R14,R_0402_1005Metric,C25870
33,"R15,R16,R17,R18,R19,R20,R21,R22,R35,R36,R50,R52,R87",R_0402_1005Metric,C25105
4.7k,"R23,R24,R25,R26,R27,R28,R37,R39,R85,R86,R96,R97",R_0402_1005Metric,C25900
10k,"R29,R33,R34,R41,R42,R43,R45,R47,R58,R59,R60,R61,R62,R63,R64,R65,R66,R67,R68,R69,R70,R71,R72,R73,R74,R76,R78,R79,R83,R94,R95,R99",R_0402_1005Metric,C25744
47k,"R38,R40",R_0402_1005Metric,C25792
12k,"R44,R46",R_0402_1005Metric,C25752
470,"R54,R55,R56,R57,R75,R77,R80",R_0402_1005Metric,C25117
2k,"R81,R82,R92,R93",R_0402_1005Metric,C4109
27k,R84,R_0402_1005Metric,C25771
2.2,"R88,R89",R_0402_1005Metric,C2909330
82.5k,R90,R_0402_1005Metric,C11717
7.06k,R98,R_0402_1005Metric,C853722
220,"R100,R101,R102,R103,R104,R105,R106,R107,R108,R109,R110,R111,R112",R_0402_1005Metric,C25091
1k,R113,R_0402_1005Metric,C11702
33,"RN1,RN2,RN3",RES-ARRAY-SMD_0402-8P-L2.0-W1.0-BL,C25501
TS-1187A-B-A-B,"SW1,SW2,SW3",SW-SMD_4P-L5.1-W5.1-P3.70-LS6.5-TL_H1.5,C318884
ADV7181DBCPZ-RL,U1,LFCSP-64_L9.0-W9.0-P0.50-BL-EP7.1,C514378
SN65DP159RGZR,U2,VQFN-48_L7.0-W7.0-P0.50-BL-EP4.1,C179676
PCM1808PWR,U3,TSSOP-14_L5.0-W4.4-P0.65-LS6.4-BL,C55513
TLV62569DBVR,"U4,U7",SOT-23-5_L3.0-W1.7-P0.95-LS2.8-BR,C141836
TPS7A7001DDAR,"U5,U6",SOIC-8_L4.9-W3.9-P1.27-LS6.0-BL-EP,C60719
TPD4E05U06DQAR,"U8,U9,U10,U19,U20",USON-10_L2.5-W1.0-P0.50-BL,C138714
TPS7A2045PDBVR,U12,SOT-23-5_L2.9-W1.6-P0.95-LS2.8-BR,C2873627
SN74LVC1GU04DBVR,U13,SOT-23-5_L3.0-W1.7-P0.95-LS2.8-BR,C81934
SN74LVC1G04DBVR,"U14,U15",SOT-23-5_L3.0-W1.7-P0.95-LS2.8-BR,C7827
MS5351M,U17,MSOP-10_L3.0-W3.0-P0.50-LS5.0-BL,C1509083
ME6211C25M5G-N,U18,SOT-23-5_L3.0-W1.7-P0.95-LS2.8-BR,C194395
SN74LVC2G17DBVR,U21,SOT-23-6_L2.9-W1.6-P0.95-LS2.8-BL,C10429
SN74LVC8T245PWR,U22,TSSOP-24_L7.8-W4.4-P0.65-LS6.4-BL,C27643
SN74AVC4T245PWR,U23,TSSOP-16_L5.0-W4.4-P0.65-LS6.4-BL,C81461
ME6211C30M5G-N,U24,SOT-23-5_L2.9-W1.6-P0.95-LS2.8-BL,C403651
28.63636MHz 20pF,Y1,CRYSTAL-SMD_L5.0-W3.2,C112564
25MHz 10pF,Y2,CRYSTAL-SMD_4P-L2.0-W1.6-BL,C5265839
